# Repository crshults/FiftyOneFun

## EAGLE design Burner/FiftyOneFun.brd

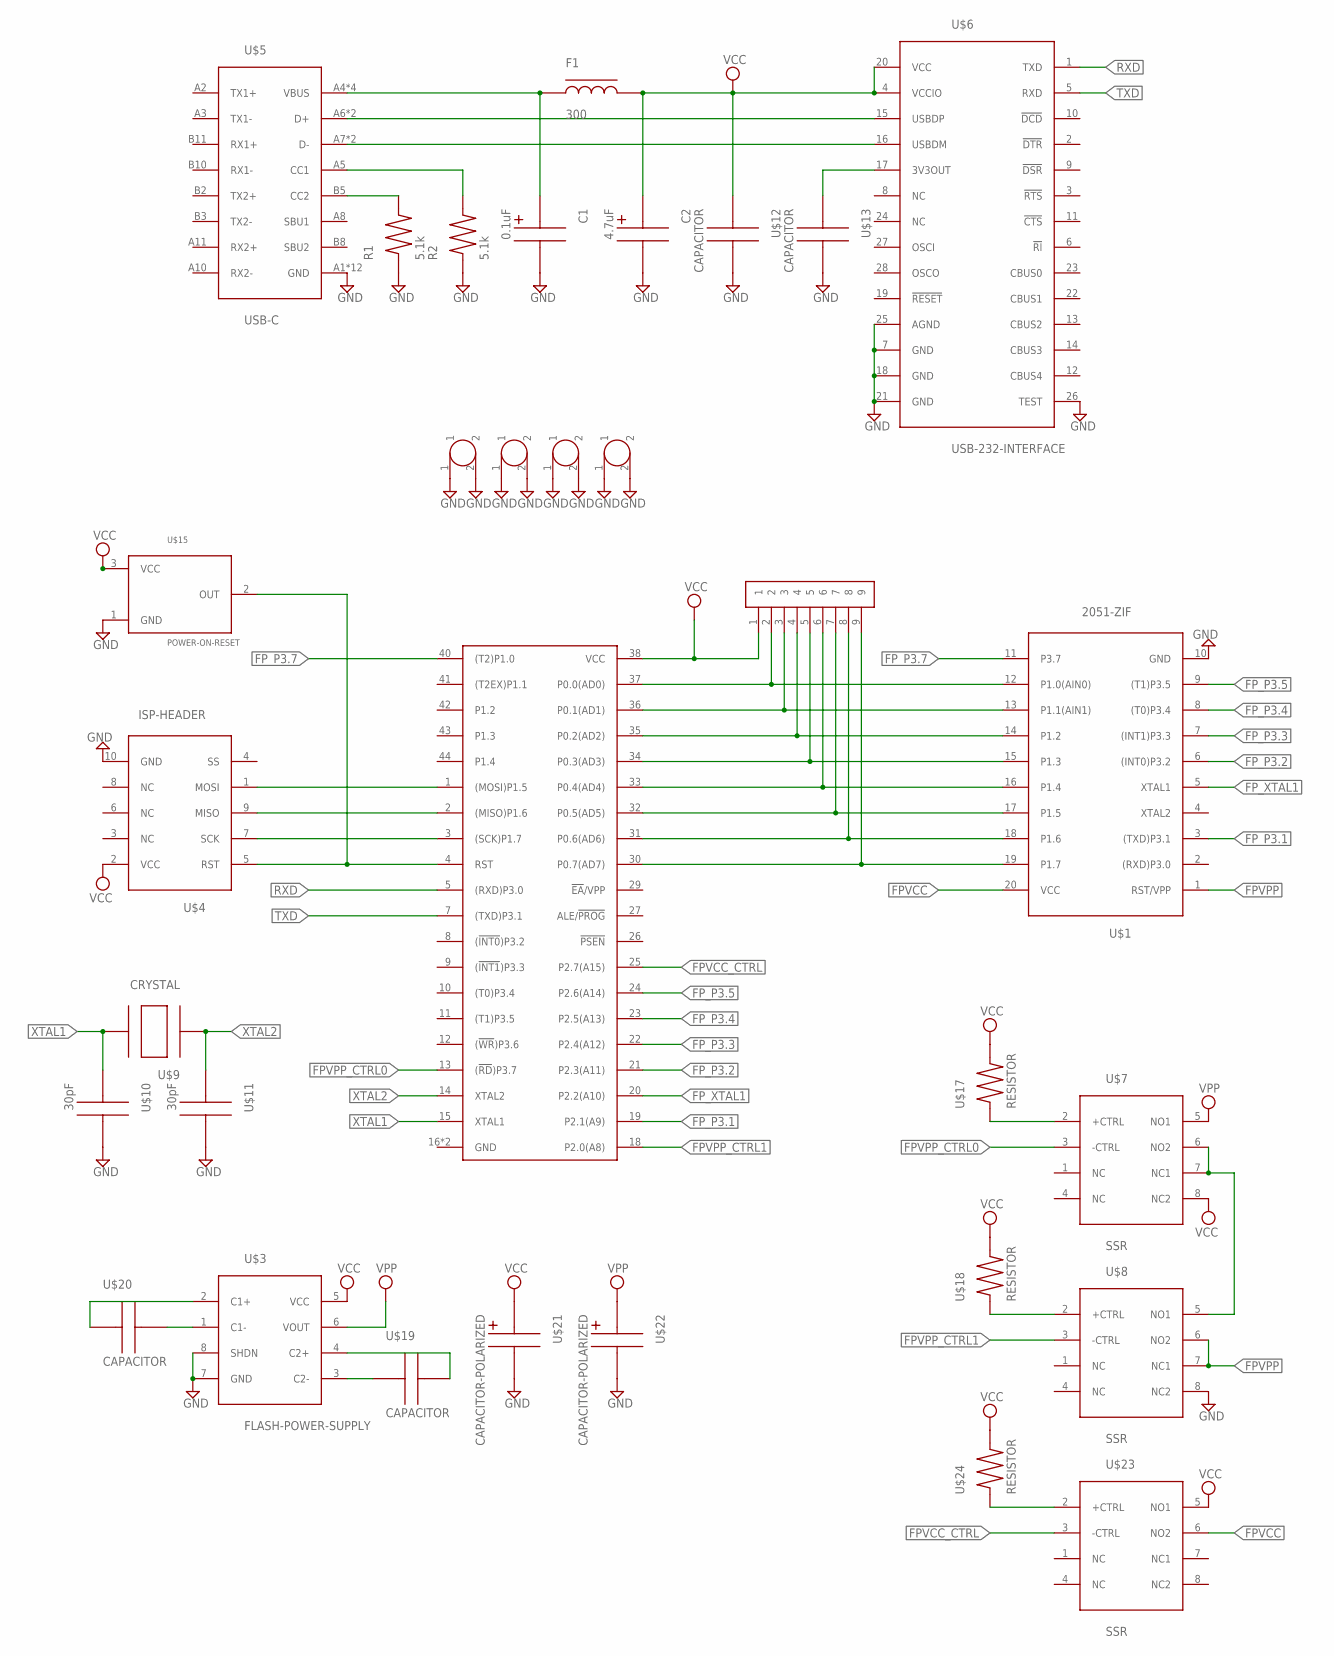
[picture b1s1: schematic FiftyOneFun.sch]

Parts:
C1: 0.1uF; CAPACITOR-POLARIZED
C2: 4.7uF; CAPACITOR-POLARIZED
F1: 300; FERRITE-BEAD
R1, R2: 5.1k; RESISTOR
U$1: 2051-ZIF
U$2: SIP-RESISTORS
U$3: FLASH-POWER-SUPPLY
U$4: ISP-HEADER
U$5: USB-C; 12401598E4#2A
U$6: USB-232-INTERFACE
U$7, U$8, U$23: SSR
U$9: CRYSTAL
U$10, U$11: 30pF; CAPACITOR
U$12, U$13, U$19, U$20: CAPACITOR
U$14: 8052
U$15: POWER-ON-RESET
U$16, U$25, U$26, U$27: MOUNTING-HOLE
U$17, U$18, U$24: RESISTOR
U$21, U$22: CAPACITOR-POLARIZED

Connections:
FPD0: U$1.12 (P1.0(AIN0)), U$2.2, U$14.37 (P0.0(AD0))
FPD1: U$1.13 (P1.1(AIN1)), U$2.3, U$14.36 (P0.1(AD1))
FPD2: U$1.14 (P1.2), U$2.4, U$14.35 (P0.2(AD2))
FPD3: U$1.15 (P1.3), U$2.5, U$14.34 (P0.3(AD3))
FPD4: U$1.16 (P1.4), U$2.6, U$14.33 (P0.4(AD4))
FPD5: U$1.17 (P1.5), U$2.7, U$14.32 (P0.5(AD5))
FPD6: U$1.18 (P1.6), U$2.8, U$14.31 (P0.6(AD6))
FPD7: U$1.19 (P1.7), U$2.9, U$14.30 (P0.7(AD7))
FPVCC: U$1.20 (VCC), U$23.6 (NO2)
FPVCC_CTRL: U$14.25 (P2.7(A15)), U$23.3 (-CTRL)
FPVPP: U$1.1 (RST/VPP), U$8.6 (NO2), U$8.7 (NC1)
FPVPP_CTRL0: U$7.3 (-CTRL), U$14.13 ((!RD!)P3.7)
FPVPP_CTRL1: U$8.3 (-CTRL), U$14.18 (P2.0(A8))
FP_P3.1: U$1.3 ((TXD)P3.1), U$14.19 (P2.1(A9))
FP_P3.2: U$1.6 ((INT0)P3.2), U$14.21 (P2.3(A11))
FP_P3.3: U$1.7 ((INT1)P3.3), U$14.22 (P2.4(A12))
FP_P3.4: U$1.8 ((T0)P3.4), U$14.23 (P2.5(A13))
FP_P3.5: U$1.9 ((T1)P3.5), U$14.24 (P2.6(A14))
FP_P3.7: U$1.11 (P3.7), U$14.40 ((T2)P1.0)
FP_XTAL1: U$1.5 (XTAL1), U$14.20 (P2.2(A10))
GND: C1.2, C2.2, R1.1, R2.1, U$1.10 (GND), U$3.7 (GND), U$3.8 (SHDN), U$4.10 (GND), U$5.A1 (GND), U$5.A12 (GND), U$5.B1 (GND), U$5.B12 (GND), U$5.MOUNT_1_BOTTOM (GND), U$5.MOUNT_1_TOP (GND), U$5.MOUNT_2_BOTTOM (GND), U$5.MOUNT_2_TOP (GND), U$5.MOUNT_3_BOTTOM (GND), U$5.MOUNT_3_TOP (GND), U$5.MOUNT_4_BOTTOM (GND), U$5.MOUNT_4_TOP (GND), U$6.7 (GND), U$6.18 (GND), U$6.21 (GND), U$6.25 (AGND), U$6.26 (TEST), U$8.8 (NC2), U$10.2, U$11.2, U$12.2, U$13.2, U$15.1 (GND), U$16.1, U$16.2, U$21.2, U$22.2, U$25.1, U$25.2, U$26.1, U$26.2, U$27.1, U$27.2
MISO: U$4.9 (MISO), U$14.2 ((MISO)P1.6)
MOSI: U$4.1 (MOSI), U$14.1 ((MOSI)P1.5)
unnamed: U$3.1 (C1-), U$20.2
unnamed: U$3.3 (C2-), U$19.1
unnamed: U$3.4 (C2+), U$19.2
unnamed: R1.2, U$5.B5 (CC2)
unnamed: R2.2, U$5.A5 (CC1)
unnamed: U$3.2 (C1+), U$20.1
unnamed: U$5.A6 (D+), U$5.B6 (D+), U$6.15 (USBDP)
unnamed: U$5.A7 (D-), U$5.B7 (D-), U$6.16 (USBDM)
unnamed: U$6.17 (3V3OUT), U$13.1
unnamed: U$7.2 (+CTRL), U$17.1
unnamed: U$8.2 (+CTRL), U$18.1
unnamed: U$7.6 (NO2), U$7.7 (NC1), U$8.5 (NO1)
unnamed: U$23.2 (+CTRL), U$24.1
RST: U$4.5 (RST), U$14.4 (RST), U$15.2 (OUT)
RXD: U$6.1 (TXD), U$14.5 ((RXD)P3.0)
SCK: U$4.7 (SCK), U$14.3 ((SCK)P1.7)
TXD: U$6.5 (RXD), U$14.7 ((TXD)P3.1)
VBUS: C1.1, F1.1, U$5.A4 (VBUS), U$5.A9 (VBUS), U$5.B4 (VBUS), U$5.B9 (VBUS)
VCC: C2.1, F1.2, U$2.1, U$3.5 (VCC), U$4.2 (VCC), U$6.4 (VCCIO), U$6.20 (VCC), U$7.8 (NC2), U$12.1, U$14.38 (VCC), U$15.3 (VCC), U$17.2, U$18.2, U$21.1, U$23.5 (NO1), U$24.2
VPP: U$3.6 (VOUT), U$7.5 (NO1), U$22.1
XTAL1: U$9.2, U$10.1, U$14.15 (XTAL1)
XTAL2: U$9.1, U$11.1, U$14.14 (XTAL2)

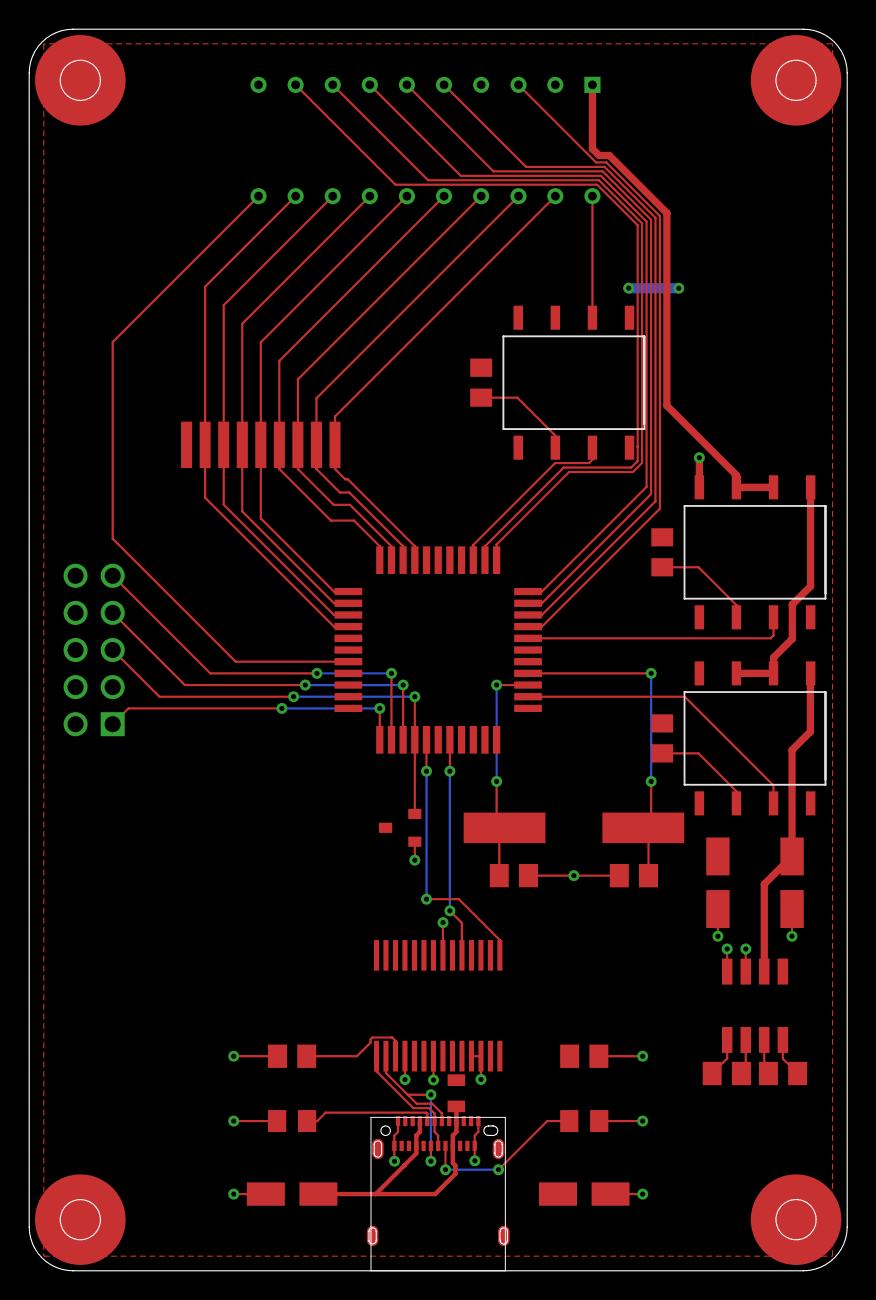
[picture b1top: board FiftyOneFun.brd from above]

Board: 2 copper layers, 56.0 x 85.0 mm, 32 parts (0 on the bottom side), 45 nets.

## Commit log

2019-03-23 Add EAGLE files for burner
